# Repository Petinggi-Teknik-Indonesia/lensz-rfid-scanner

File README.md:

# lensz-rfid-scanner
Lens'z hardware scanner based on ESP32 development board

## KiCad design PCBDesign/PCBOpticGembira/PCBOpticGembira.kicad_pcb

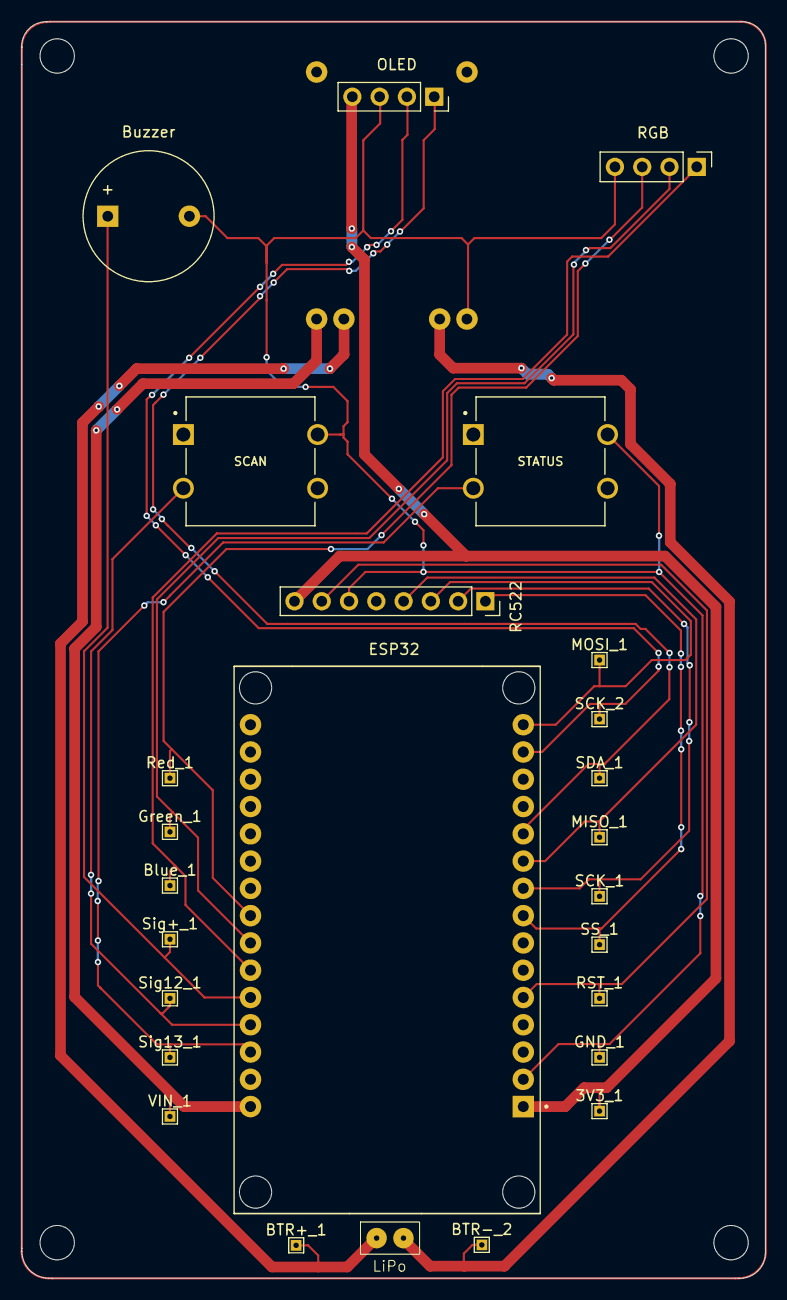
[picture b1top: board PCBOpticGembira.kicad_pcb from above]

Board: 2 copper layers, 69.3 x 117.0 mm, 27 parts (1 on the bottom side), 18 nets.

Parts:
3V3_1: 3V3_TP; TestPoint_THTPad_1.0x1.0mm_Drill0.5mm
BTR+_1: BTR+; TestPoint_THTPad_1.0x1.0mm_Drill0.5mm
BTR-_2: BTR-; TestPoint_THTPad_1.0x1.0mm_Drill0.5mm
Blue_1: Blue_TP; TestPoint_THTPad_1.0x1.0mm_Drill0.5mm
Buzzer: Buzzer; Buzzer_12x9.5RM7.6
ESP32: MODULE_ESP32_DEVKIT_V1
GND_1: GND_TP; TestPoint_THTPad_1.0x1.0mm_Drill0.5mm
Green_1: Green_TP; TestPoint_THTPad_1.0x1.0mm_Drill0.5mm
LiPo: 3.7V 3000MAh; Battery
MISO_1: MISO_TP; TestPoint_THTPad_1.0x1.0mm_Drill0.5mm
MOSI_1: MOSI_TP; TestPoint_THTPad_1.0x1.0mm_Drill0.5mm
OLED: I2C OLED Module; PinSocket_1x04_P2.54mm_Vertical
RC522: RC522 Module; PinSocket_1x08_P2.54mm_Vertical
RGB: HW479 RGB Module; PinHeader_1x04_P2.54mm_Vertical
RST_1: RST; TestPoint_THTPad_1.0x1.0mm_Drill0.5mm
Red_1: Red_TP; TestPoint_THTPad_1.0x1.0mm_Drill0.5mm
SCAN: SCAN BTN; SW_VS-1213-67-160GF
SCK_1: SCK_TP1; TestPoint_THTPad_1.0x1.0mm_Drill0.5mm
SCK_2: SCK_TP2; TestPoint_THTPad_1.0x1.0mm_Drill0.5mm
SDA_1: SDA_TP; TestPoint_THTPad_1.0x1.0mm_Drill0.5mm
SS_1: SS_TP; TestPoint_THTPad_1.0x1.0mm_Drill0.5mm
STATUS: STATUS BTN; SW_VS-1213-67-160GF
Sig12_1: Sig12_TP; TestPoint_THTPad_1.0x1.0mm_Drill0.5mm
Sig13_1: Sig13_TP; TestPoint_THTPad_1.0x1.0mm_Drill0.5mm
Sig+_1: Sig+_TP; TestPoint_THTPad_1.0x1.0mm_Drill0.5mm
TP4056: TP4056 Charging Module; TP4056-Module
VIN_1: VIN_TP; TestPoint_THTPad_1.0x1.0mm_Drill0.5mm

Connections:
+3V3: 3V3_1.1, ESP32.30 (3.3V), OLED.4, RC522.8
/BTR+: BTR+_1.1, LiPo.1 (+), TP4056.5
/BTR-: BTR-_2.1, LiPo.2 (-), TP4056.6
/Blue: Blue_1.1, ESP32.10 (GPIO27), RGB.1
/Green: ESP32.9 (GPIO26), Green_1.1, RGB.2
/MISO: ESP32.21 (GPIO19), MISO_1.1, RC522.4
/MOSI: ESP32.16 (GPIO23), MOSI_1.1, RC522.3
/Red: ESP32.8 (GPIO25), RGB.3, Red_1.1
/Reset: ESP32.26 (GPIO4), RC522.7, RST_1.1
/Serial_clock1: ESP32.22 (GPIO18), RC522.2, SCK_1.1
/Serial_clock2: ESP32.17 (GPIO22), OLED.2, SCK_2.1
/Serial_data: ESP32.20 (GPIO21), OLED.1, SDA_1.1
/Sig+: Buzzer.1, ESP32.11 (GPIO14), Sig+_1.1
/Sig_12: ESP32.12 (GPIO12), SCAN.2, Sig12_1.1
/Sig_13: ESP32.13 (GPIO13), STATUS.2, Sig13_1.1
/Slave_select: ESP32.23 (GPIO5), RC522.1, SS_1.1
/VIN: ESP32.15 (VIN), TP4056.3, VIN_1.1
GND: Buzzer.2, ESP32.29 (GND), GND_1.1, OLED.3, RC522.6, RGB.4, SCAN.3, STATUS.3, TP4056.4

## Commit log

2025-11-14 Initial RFID Scanner Logic (UTS)
    Worked on most of the logic and accomplished all of the Mid Exam Rubrics
2025-11-14 RFID Scanner Logics and Design (UAS)
    - Almost Finish Main Code
    - Almost Finish PCB Design
    - Documentation
